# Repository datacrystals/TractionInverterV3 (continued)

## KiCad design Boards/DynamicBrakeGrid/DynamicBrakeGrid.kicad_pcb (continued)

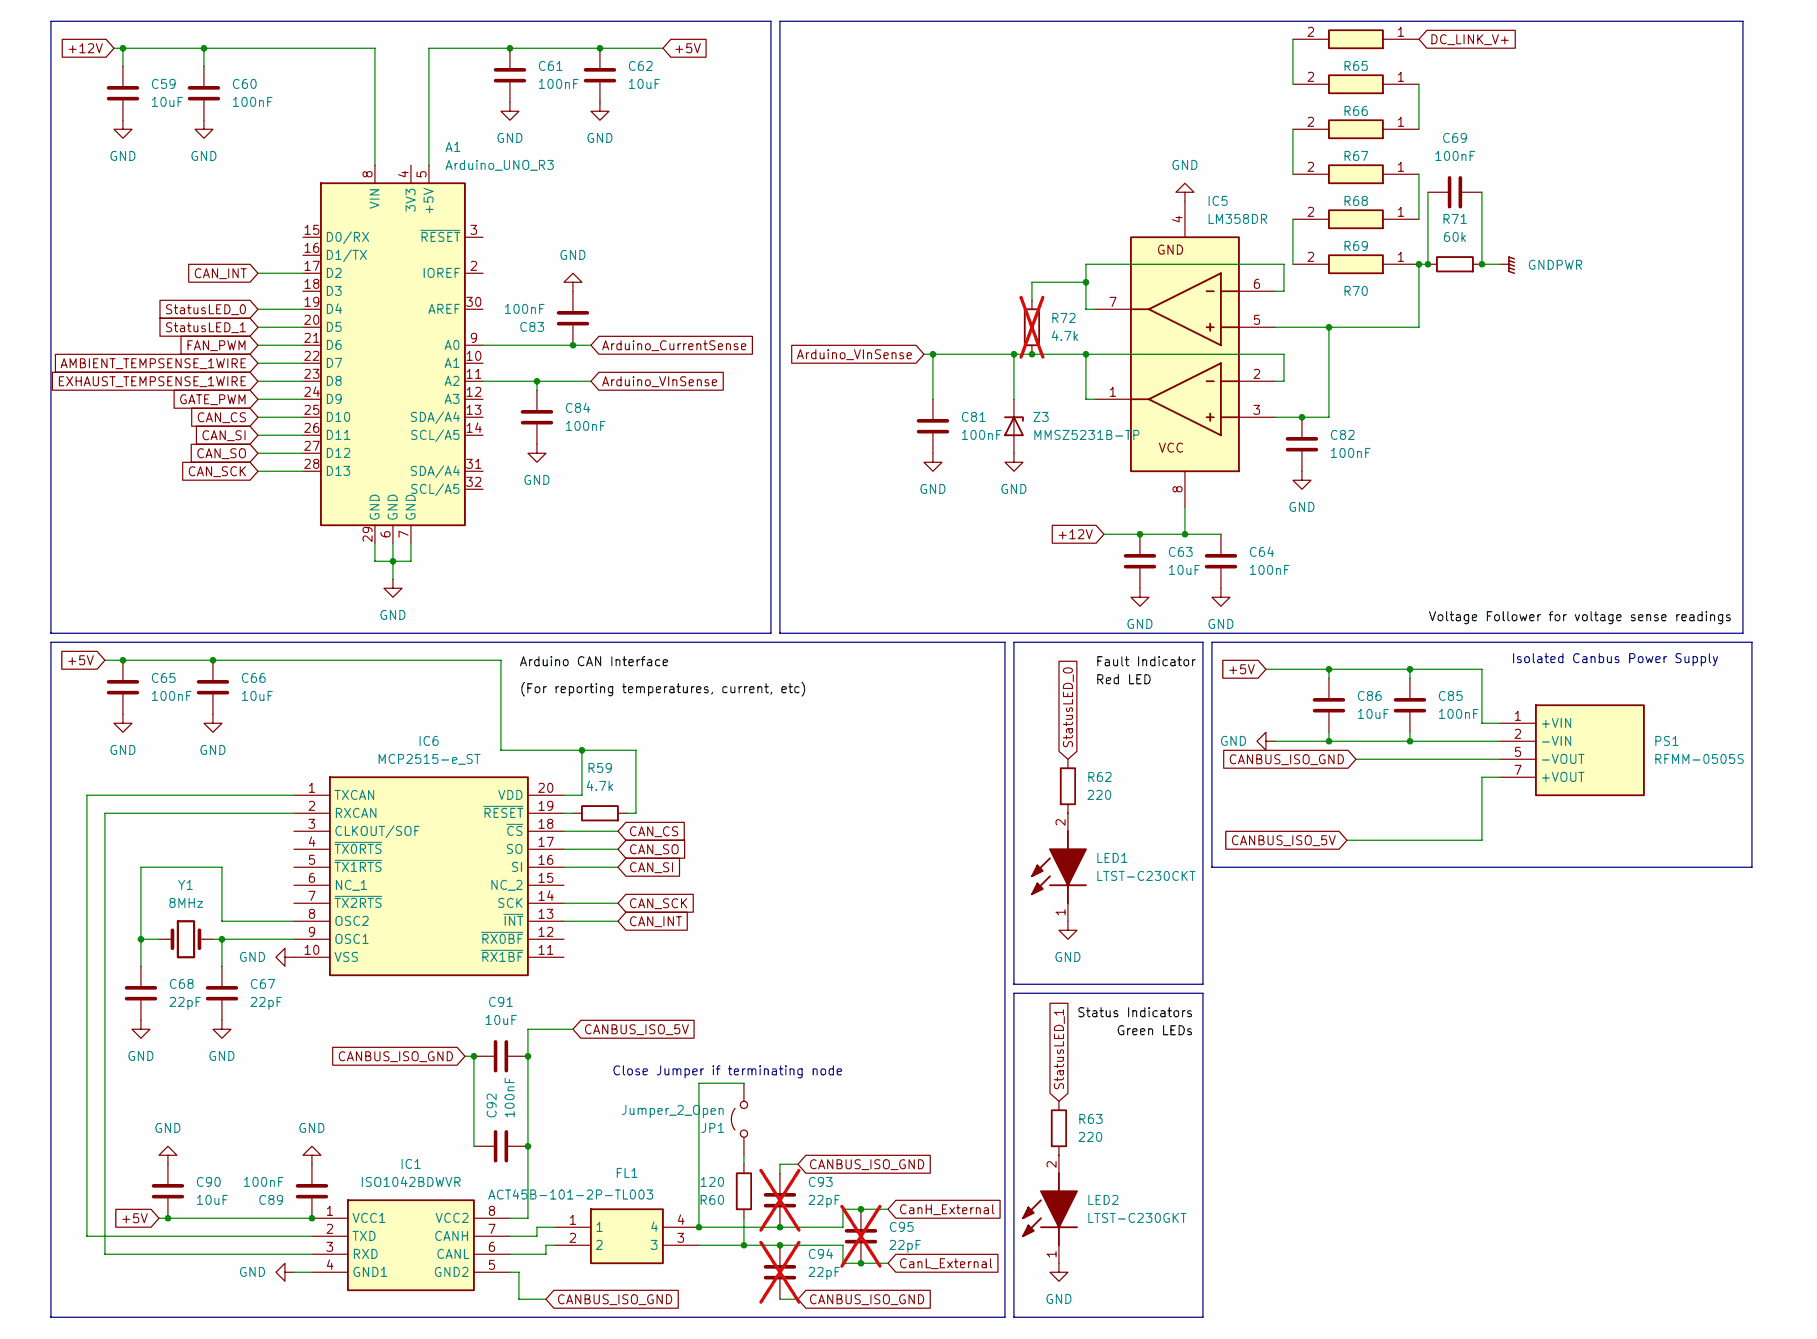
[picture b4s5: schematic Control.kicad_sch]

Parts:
A1: Arduino_UNO_R3; Arduino_UNO_R3_ModifiedCourtyard
C59, C62, C63, C66, C86, C90, C91: 10uF; C_1210_3225Metric_Pad1.33x2.70mm_HandSolder
C60, C61, C64, C65, C69, C81, C82, C83, C84, C85, C89, C92: 100nF; C_1210_3225Metric_Pad1.33x2.70mm_HandSolder
C67, C68: 22pF; C_1210_3225Metric_Pad1.33x2.70mm_HandSolder
C93, C94, C95: 22pF; C_1210_3225Metric_Pad1.33x2.70mm_HandSolder; not fitted
FL1: ACT45B-101-2P-TL003; ACT45B1012PTL003; Mouser Part Number 810-ACT45B1012PTL003
IC1: ISO1042BDWVR; SOIC127P1150X280-8N; Mouser Part Number 595-ISO1042BDWVR
IC5: LM358DR; SOIC127P600X175-8N; Mouser Part Number 595-LM358DR
IC6: MCP2515-e_ST; SOP65P640X120-20N; Mouser Part Number 579-MCP2515-E/ST
JP1: Jumper_2_Open; PinHeader_1x02_P2.54mm_Vertical
LED1: LTST-C230CKT; LEDC3216X120N; Mouser Part Number 859-LTST-C230CKT
LED2: LTST-C230GKT; LEDC3216X120N; Mouser Part Number 859-LTST-C230GKT
PS1: RFMM-0505S; RFMM0505S; Mouser Part Number 919-RFMM-0505S
R59: 4.7k; R_1210_3225Metric_Pad1.30x2.65mm_HandSolder
R60: 120; R_1210_3225Metric_Pad1.30x2.65mm_HandSolder
R62, R63: 220; R_1210_3225Metric_Pad1.30x2.65mm_HandSolder
R65, R66, R67, R68, R69, R70: RC2512JK-071ML; RESC6431X65N; Mouser Part Number 603-RC2512JK-071ML
R71: 60k; R_1210_3225Metric_Pad1.30x2.65mm_HandSolder
R72: 4.7k; R_1210_3225Metric_Pad1.30x2.65mm_HandSolder; not fitted
Y1: 8MHz; Crystal_HC49-4H_Vertical
Z3: MMSZ5231B-TP; SOD3716X135N; Mouser Part Number 833-MMSZ5231B-TP

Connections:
+5V: A1.5 (+5V), C61.1, C62.1, C65.1, C66.1, C85.1, C86.1, C89.1, C90.2, IC1.1 (VCC1), IC6.20 (VDD), PS1.1 (+VIN), R59.2; also elsewhere on the board
+12V: A1.8 (VIN), C59.1, C60.1, C63.1, C64.1, IC5.8 (V+); also elsewhere on the board
AMBIENT_TEMPSENSE_1WIRE: A1.22 (D7); also elsewhere on the board
Arduino_CurrentSense: A1.9 (A0), C83.1; also elsewhere on the board
Arduino_VInSense: A1.11 (A2), C81.1, C84.1, IC5.1 (OUT1), IC5.2 (IN1-), R72.1, Z3.1 (K)
CANBUS_ISO_5V: C91.1, C92.2, IC1.8 (VCC2), PS1.7 (+VOUT)
CANBUS_ISO_GND: C91.2, C92.1, C93.1, C94.2, IC1.5 (GND2), PS1.5 (-VOUT); also elsewhere on the board
CAN_CS: A1.25 (D10), IC6.18 (~CS)
CAN_INT: A1.17 (D2), IC6.13 (~INT)
CAN_SCK: A1.28 (D13), IC6.14 (SCK)
CAN_SI: A1.26 (D11), IC6.16 (SI)
CAN_SO: A1.27 (D12), IC6.17 (SO)
CanH_External: C93.2, C95.1, FL1.4, JP1.2 (B); also elsewhere on the board
CanL_External: C94.1, C95.2, FL1.3, R60.2; also elsewhere on the board
DC_LINK_V+: R65.1; also elsewhere on the board
EXHAUST_TEMPSENSE_1WIRE: A1.23 (D8); also elsewhere on the board
FAN_PWM: A1.21 (D6); also elsewhere on the board
GATE_PWM: A1.24 (D9); also elsewhere on the board
GND: A1.6 (GND), A1.7 (GND), A1.29 (GND), C59.2, C60.2, C61.2, C62.2, C63.2, C64.2, C65.2, C66.2, C67.2, C68.2, C81.2, C82.2, C83.2, C84.2, C85.2, C86.2, C89.2, C90.1, IC1.4 (GND1), IC5.4 (V-), IC6.10 (VSS), LED1.1 (K), LED2.1 (K), PS1.2 (-VIN), Z3.2 (A); also elsewhere on the board
GNDPWR: C69.2, R71.2; also elsewhere on the board
unnamed: FL1.1, IC1.7 (CANH)
unnamed: FL1.2, IC1.6 (CANL)
unnamed: IC1.3 (RXD), IC6.2 (RXCAN)
unnamed: IC1.2 (TXD), IC6.1 (TXCAN)
unnamed: C69.1, C82.1, IC5.3 (IN1+), IC5.5 (IN2+), R70.1, R71.1
unnamed: IC5.6 (IN2-), IC5.7 (OUT2), R72.2
unnamed: C67.1, IC6.9 (OSC1), Y1.2
unnamed: C68.1, IC6.8 (OSC2), Y1.1
unnamed: IC6.19 (~RESET), R59.1
unnamed: JP1.1 (A), R60.1
unnamed: LED1.2 (A), R62.2
unnamed: LED2.2 (A), R63.2
unnamed: R65.2, R66.2
unnamed: R66.1, R67.1
unnamed: R67.2, R68.2
unnamed: R68.1, R69.1
unnamed: R69.2, R70.2
StatusLED_0: A1.19 (D4), R62.1
StatusLED_1: A1.20 (D5), R63.1

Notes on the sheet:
Close Jumper if terminating node
Isolated Canbus Power Supply

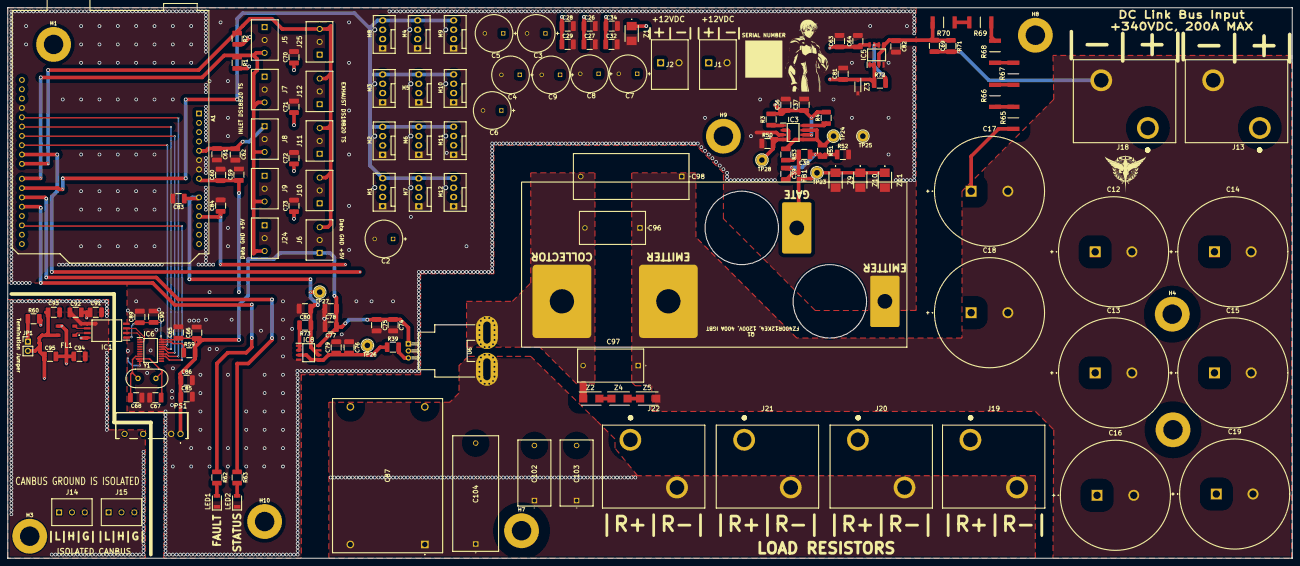
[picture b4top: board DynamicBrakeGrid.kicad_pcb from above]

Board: 4 copper layers, 350.0 x 150.0 mm, 159 parts (0 on the bottom side), 52 nets.

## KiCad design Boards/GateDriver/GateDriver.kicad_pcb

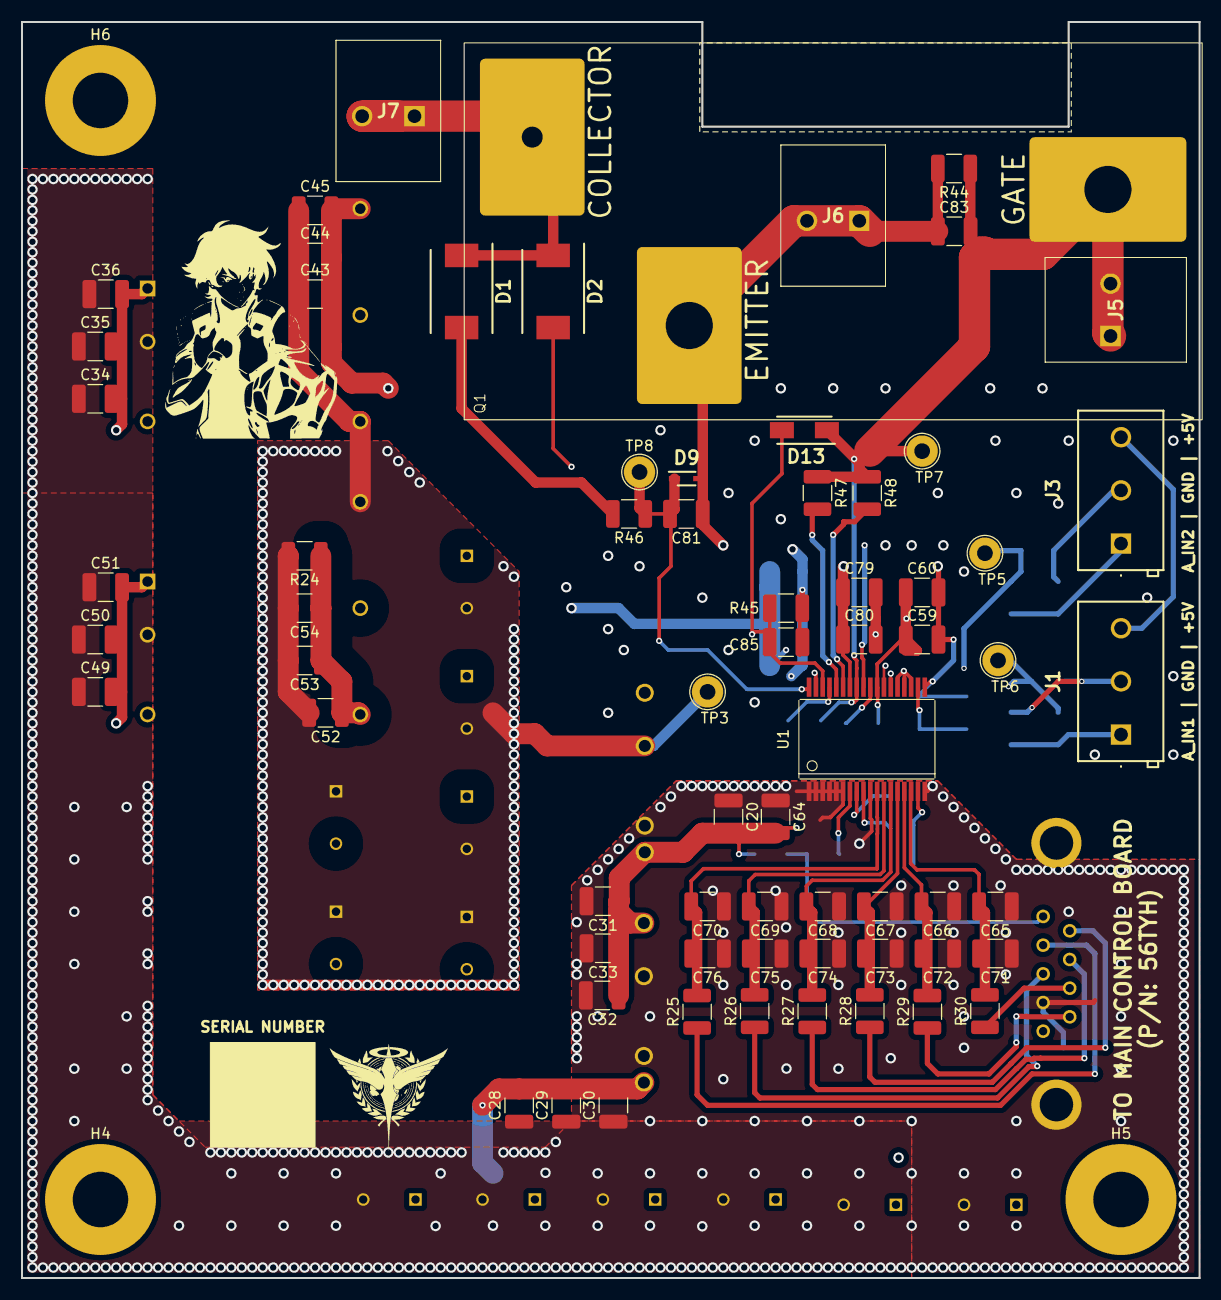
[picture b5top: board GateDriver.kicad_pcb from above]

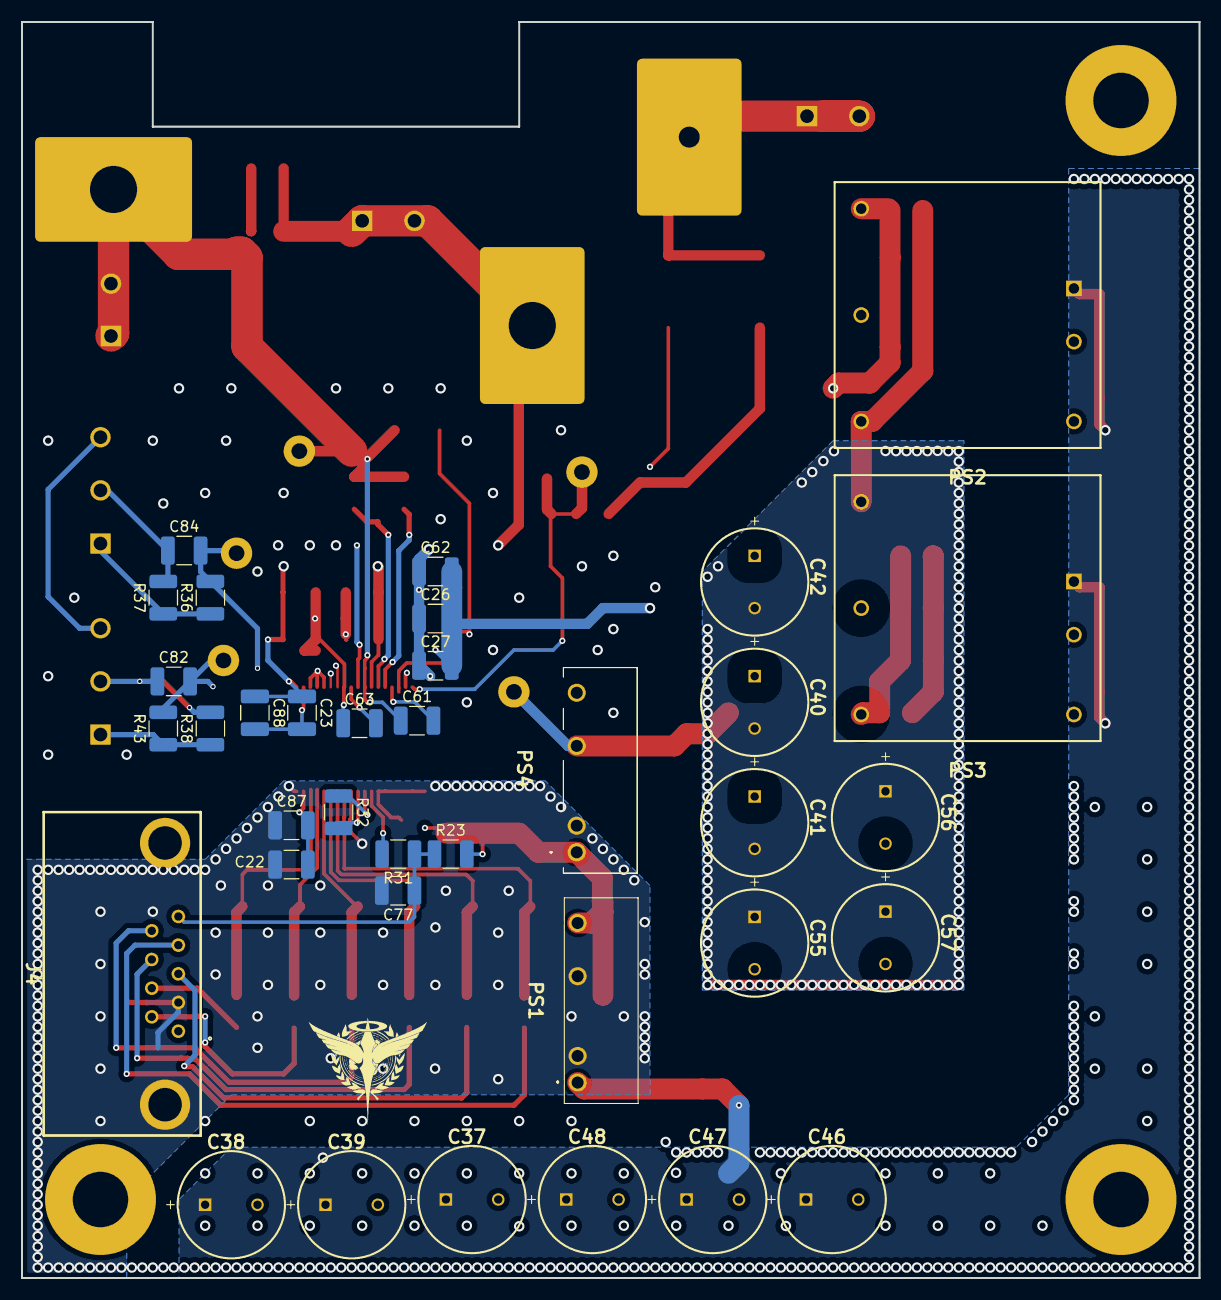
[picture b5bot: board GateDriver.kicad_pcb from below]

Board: 4 copper layers, 112.5 x 120.0 mm, 106 parts (36 on the bottom side), 37 nets.

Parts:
C20, C26, C29, C32, C35, C44, C50, C53, C59, C63, C80: 1uF; C_1210_3225Metric_Pad1.33x2.70mm_HandSolder
C22, C23: 4.7uF; C_1210_3225Metric_Pad1.33x2.70mm_HandSolder
C27, C30, C33, C36, C45, C51, C52, C60, C61, C64, C79, C83, C87, C88: 100nF; C_1210_3225Metric_Pad1.33x2.70mm_HandSolder
C28, C31, C34, C43, C49, C54, C62: 10uF; C_1210_3225Metric_Pad1.33x2.70mm_HandSolder
C37, C38, C39, C40, C41, C42, C46, C47, C48, C55, C56, C57: UVY1E102MPD1TD; CAPPRD500W60D1025H1750
C65, C66, C67, C68, C69, C70: 10pF; C_1210_3225Metric_Pad1.33x2.70mm_HandSolder
C71, C72, C73, C74, C75, C76, C77, C81: 100pF; C_1210_3225Metric_Pad1.33x2.70mm_HandSolder
C82, C84: 10nF; C_1210_3225Metric_Pad1.33x2.70mm_HandSolder
C85: 2.2nF; C_1210_3225Metric_Pad1.33x2.70mm_HandSolder
D1, D2: S3N; DIOM8059X265N
D9: BAT54WS-7-F; SOD2513X120N
D13: MBRA340T3G; DIOM5226X220N
H4, H5, H6: MountingHole_Pad_MP; MountingHole_5.3mm_M5_Pad
J1, J3: 1548129
J4: 5-106505-2; 5-106505-2_3
J5, J6, J7: 1987724
PS1: RKE-1205S_H; RKE1205SH
PS2: REC10K-2415SAW_H2; REC10K-AW
PS3: REC10K-2409SAW_H2; REC10K-AW
PS4: RFMM-0505S; RFMM0505S
Q1: CM600HA-24H-Gate
R23, R32, R37, R38: 10k; R_1210_3225Metric_Pad1.30x2.65mm_HandSolder
R24, R36, R43: 0; R_1210_3225Metric_Pad1.30x2.65mm_HandSolder
R25, R26, R27, R28, R29, R30, R31, R45: 100; R_1210_3225Metric_Pad1.30x2.65mm_HandSolder
R44, R46: 1k; R_1210_3225Metric_Pad1.30x2.65mm_HandSolder
R47, R48: 1.5; R_1210_3225Metric_Pad1.30x2.65mm_HandSolder
TP3, TP5, TP6, TP7, TP8: TestPoint; TestPoint_Loop_D2.54mm_Drill1.5mm_Beaded
U1: UCC5870QDWJRQ1; DWJ0036A

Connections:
+5V: C20.2, C31.1, C32.1, C33.1, C64.2, PS1.7 (+VOUT), PS4.1 (+VIN), R23.2, R32.2, U1.9 (VCC1)
+5VP: J1.3, J3.3, PS4.7 (+VOUT)
+12V: C28.2, C29.2, C30.2, C34.2, C35.2, C36.2, C37.1 (+), C38.1 (+), C39.1 (+), C46.1 (+), C47.1 (+), C48.1 (+), C49.2, C50.2, C51.2, J4.1, PS1.1 (+VIN), PS2.1 (+VIN), PS3.1 (+VIN)
ANALOG_INPUT_1: J1.1, R38.1, R43.1
ANALOG_INPUT_2: J3.1, R36.1, R37.1
ANALOG_SENSE_1: C82.2, R43.2, TP6.1, U1.25 (AI2)
ANALOG_SENSE_2: C84.2, R36.2, TP5.1, U1.24 (AI3)
FAULT: C77.1, J4.5, R23.1, R31.1
FILTERED_GATE_DRIVE+: C69.2, C75.2, R26.2, U1.12 (IN+)
FILTERED_GATE_DRIVE-: C70.2, C76.2, R25.2, U1.11 (IN-)
FILTERED_SDI: C66.2, C72.2, R29.2, U1.15 (SDI)
FILTERED_SDO: C65.2, C71.2, R30.2, U1.16 (SDO)
FILTERED_SPI_CLK: C68.2, C74.2, R27.2, U1.13 (CLK)
FILTERED_SPI_CS: C67.2, C73.2, R28.2, U1.14 (nCS)
GATE_DRIVE+: J4.3, R26.1
GATE_DRIVE-: J4.4, R25.1
GND: C20.1, C22.1, C28.1, C29.1, C30.1, C31.2, C32.2, C33.2, C34.1, C35.1, C36.1, C37.2 (-), C38.2 (-), C39.2 (-), C46.2 (-), C47.2 (-), C48.2 (-), C49.1, C50.1, C51.1, C64.1, C65.1, C66.1, C67.1, C68.1, C69.1, C70.1, C71.1, C72.1, C73.1, C74.1, C75.1, C76.1, C77.2, C87.1, J4.2, J4.10, J4.11, PS1.2 (-VIN), PS1.5 (-VOUT), PS2.2 (-VIN), PS3.2 (-VIN), PS4.2 (-VIN), U1.1 (GND1), U1.2 (NC), U1.3 (NC), U1.4 (NC), U1.5 (NC), U1.6 (ASC_EN), U1.10 (ASC), U1.18 (GND1)
IGBT_COLLECTOR: D1.1 (K), D2.1 (K), J7.1, J7.2, Q1.1 (C)
IGBT_EMITTER: C26.1, C27.1, C40.2 (-), C41.2 (-), C42.2 (-), C43.1, C44.1, C45.1, C52.2, C53.2, C54.2, C55.1 (+), C56.1 (+), C57.1 (+), C59.1, C60.1, C62.1, C63.1, C81.1, C82.1, C83.1, C84.1, C85.2, D9.2 (A), J1.2, J3.2, J6.1, J6.2, PS2.4 (-VOUT), PS3.6 (+VOUT), PS4.5 (-VOUT), Q1.2 (E), R24.2, R37.2, R38.2, R44.2, R45.1, TP3.1, U1.21 (AI6), U1.22 (AI5), U1.23 (AI4), U1.26 (AI1), U1.28 (GND2)
IGBT_GATE: C61.1, C83.2, D13.1 (K), J5.1, J5.2, Q1.3 (G), R44.1, R47.1, R48.1, TP7.1, U1.29 (CLAMP)
ISO_GATE_DRIVE_+15V: C26.2, C27.2, C40.1 (+), C41.1 (+), C42.1 (+), C43.2, C44.2, C45.2, C62.2, C79.2, C80.2, PS2.6 (+VOUT), U1.35 (VCC2)
ISO_GATE_DRIVE_-9V: C23.1, C52.1, C53.1, C54.1, C55.2 (-), C56.2 (-), C57.2 (-), C59.2, C60.2, C79.1, C80.1, C88.1, PS3.4 (-VOUT), R24.1, U1.19 (VEE2), U1.30 (VEE2)
unnamed: D1.2 (A), R46.2
unnamed: C81.2, D9.1 (K), R46.1, TP8.1, U1.36 (DESAT)
unnamed: C85.1, D2.2 (A), D13.2 (A), R45.2, U1.34 (VCECLP)
unnamed: R47.2, U1.32 (OUTH)
unnamed: R48.2, U1.31 (OUTL)
unnamed: C61.2, U1.33 (VBST)
unnamed: C63.2, U1.27 (VREF)
unnamed: C22.2, C87.2, U1.17 (VREG1)
unnamed: C23.2, C88.2, U1.20 (VREG2)
unnamed: R31.2, U1.7 (nFLT1)
unnamed: R32.1, U1.8 (nFLT2_DOUT)
SDI: J4.6, R29.1
SDO: J4.7, R30.1
SPI_CLK: J4.8, R27.1
SPI_CS: J4.9, R28.1

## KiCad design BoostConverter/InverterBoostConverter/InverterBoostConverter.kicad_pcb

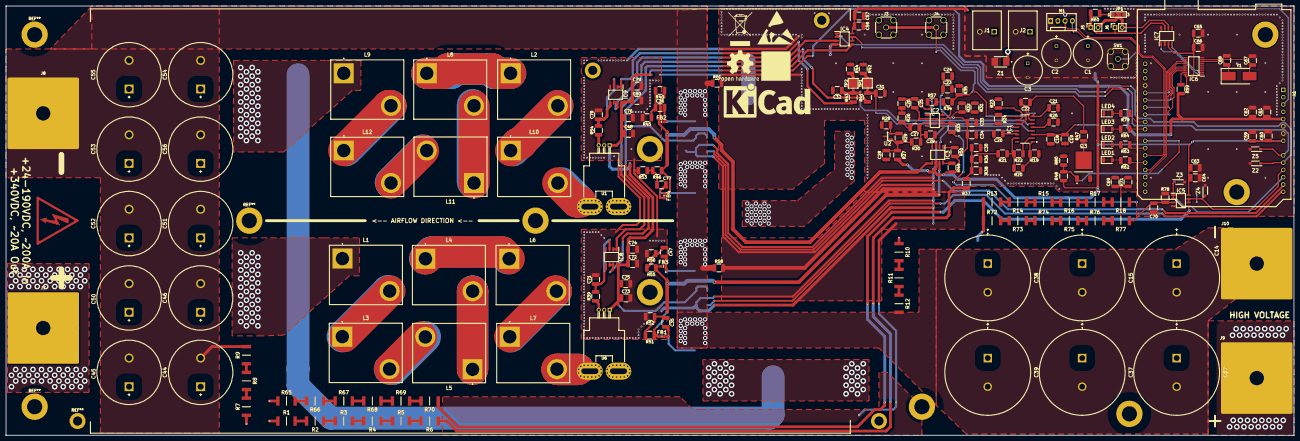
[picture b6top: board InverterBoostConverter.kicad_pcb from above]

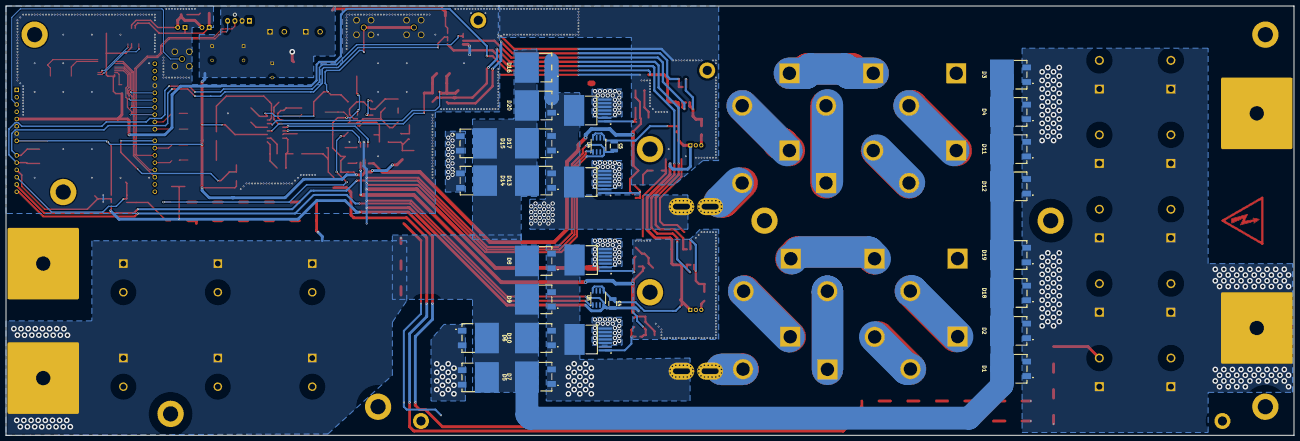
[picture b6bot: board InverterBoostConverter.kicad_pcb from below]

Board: 2 copper layers, 450.0 x 150.0 mm, 227 parts (28 on the bottom side), 121 nets.

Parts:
A1: Arduino_UNO_R3; Arduino_UNO_R3_ModifiedCourtyard
C1, C2, C3: 1000uF; CAPPRD500W60D1025H1750
C4, C5, C20, C22: 1uF; C_1210_3225Metric_Pad1.33x2.70mm_HandSolder
C14, C15, C17, C37, C38, C39: 75uF; ALH82A750CB600
C18, C23, C34, C48, C58, C60, C61, C64, C65, C69, C70, C73, C74, C79: 100nF; C_1210_3225Metric_Pad1.33x2.70mm_HandSolder
C19, C24, C33, C57, C59, C62, C63, C66, C72, C75, C76, C80: 10uF; C_1210_3225Metric_Pad1.33x2.70mm_HandSolder
C21: 180pF; C_1210_3225Metric_Pad1.33x2.70mm_HandSolder
C25: 10nF; C_1210_3225Metric_Pad1.33x2.70mm_HandSolder
C26: C_1210_3225Metric_Pad1.33x2.70mm_HandSolder
C27, C29, C30, C35, C36, C47, C77: 1nF; C_1210_3225Metric_Pad1.33x2.70mm_HandSolder
C28: 4.7uF; C_1210_3225Metric_Pad1.33x2.70mm_HandSolder
C31, C32, C71, C78: 470pF; C_1210_3225Metric_Pad1.33x2.70mm_HandSolder
C44, C45, C46, C50, C51, C52, C53, C54, C55, C56: 330uF; CAPPRD1000W190D2250H2700
C67, C68: 22pF; C_1210_3225Metric_Pad1.33x2.70mm_HandSolder
D1, D2, D3, D4, D5, D6, D7, D8, D9, D10, D11, D12, D13, D14, D15, D16, D17, D18, D19, D20: VS-30CDU06HM3_I; VS30CDU06HM3I
FB1, FB2, FB3, FB4: FBMJ1608HS220NTR; BEADC1608X100N
IC1: UCC28220D
IC2, IC4, IC5, IC8, IC9: LM358DR; SOIC127P600X175-8N
IC3: UCC27424QDRQ1; SOIC127P600X175-8N
IC6: MCP2515-e_ST; SOP65P640X120-20N
IC7: TJA1050T_CM,118; SOIC127P600X175-8N
J1, J2: 1987724
J3, J4: Conn_Coaxial; SMA_Wurth_60312002114503_Vertical
J5, J6: Conn_01x02_Pin; PinSocket_1x02_P2.54mm_Vertical
J7, J8, J9, J10: WireSolderJoint
JP1: Jumper_2_Bridged; SolderJumper-3_P2.0mm_Open_TrianglePad1.0x1.5mm_NumberLabels
L1, L2, L3, L4, L5, L6, L7, L8, L9, L10, L11, L12: IHDM1008BCEV2R2M20
LED1: LTST-C230CKT; LEDC3216X120N
LED2, LED3, LED4: LTST-C230GKT; LEDC3216X120N
M1: Fan_4pin; FanPinHeader_1x04_P2.54mm_Vertical
Q1, Q2, Q4, Q5: IMBG65R015M2H; TO127P1500X470-8N-2-V1
Q3: SIHFR120-GE3; SIHFR120GE3
R1, R2, R3, R4, R5, R6, R7, R8, R9, R10, R11, R12, R13, R14, R15, R16, R17, R18, R65, R66, R67, R68, R69, R72, R73, R74, R75, R76: RC2512JK-071ML; RESC6431X65N
R19: 12.79k; R_1210_3225Metric_Pad1.30x2.65mm_HandSolder
R20: 101.85k; R_1210_3225Metric_Pad1.30x2.65mm_HandSolder
R21: 149.21k; R_1210_3225Metric_Pad1.30x2.65mm_HandSolder
R22, R26, R37, R49, R50, R80: 100k; R_1210_3225Metric_Pad1.30x2.65mm_HandSolder
R23: 40.8k; R_1210_3225Metric_Pad1.30x2.65mm_HandSolder
R24: 10.2k; R_1210_3225Metric_Pad1.30x2.65mm_HandSolder
R25: 7k; R_1210_3225Metric_Pad1.30x2.65mm_HandSolder
R27: 5.6k; R_1210_3225Metric_Pad1.30x2.65mm_HandSolder
R28, R40, R46, R47, R51, R55, R59: 10k; R_1210_3225Metric_Pad1.30x2.65mm_HandSolder
R29, R30, R41, R43, R58, R61: 0; R_1210_3225Metric_Pad1.30x2.65mm_HandSolder
R31: 45.00k; R_1210_3225Metric_Pad1.30x2.65mm_HandSolder
R32, R71: 120k; R_1210_3225Metric_Pad1.30x2.65mm_HandSolder
R33: 28k; R_1210_3225Metric_Pad1.30x2.65mm_HandSolder
R34, R35, R57: 1k; R_1210_3225Metric_Pad1.30x2.65mm_HandSolder
R36: 800.00k; R_1210_3225Metric_Pad1.30x2.65mm_HandSolder
R38, R42, R44: R_1210_3225Metric_Pad1.30x2.65mm_HandSolder
R39, R54: 4.7k; R_1210_3225Metric_Pad1.30x2.65mm_HandSolder
R45, R52, R53, R56: 1; R_1210_3225Metric_Pad1.30x2.65mm_HandSolder
R48: 300k; R_1210_3225Metric_Pad1.30x2.65mm_HandSolder
R60: 120; R_1210_3225Metric_Pad1.30x2.65mm_HandSolder
R62, R63, R64, R79: 220; R_1210_3225Metric_Pad1.30x2.65mm_HandSolder
R70, R77: 1M; RESC6431X65N
R78: 40k; R_1210_3225Metric_Pad1.30x2.65mm_HandSolder
SW1: SW_Push; SMA_Wurth_60312002114503_Vertical
TP1, TP2: TestPoint; TestPoint_Pad_3.0x3.0mm
U1, U6: ACS758xCB-200U-PFF; Allegro_CB_PFF
U2: TL431AIDBZR; SOT95P237X112-3N
U4, U5: TMP36xS; SOIC-8_3.9x4.9mm_P1.27mm
Y1: 8MHz; Crystal_SMD_7050-2Pin_7.0x5.0mm_HandSoldering
Z1: 1SMB2EZ15_R1_00001
Z2, Z3, Z4, Z5: MMSZ5231B-TP; SOD3716X135N

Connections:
+5V: A1.5 (+5V), C4.1, C5.1, C48.1, C61.1, C62.1, C65.1, C66.1, C72.1, C73.1, C74.1, C75.1, C76.1, C79.1, C80.1, IC6.20 (VDD), IC7.3 (VCC), IC8.8 (V+), IC9.8 (V+), R59.2, U1.1 (VCC), U4.5 (~SHUTDOWN), U4.8 (+Vs), U5.5 (~SHUTDOWN), U5.8 (+Vs), U6.1 (VCC)
+12V: A1.8 (VIN), C1.1 (+), C2.1 (+), C3.1 (+), C18.1, C19.1, C23.1, C24.1, C33.1, C34.1, C57.1, C58.1, C59.1, C60.1, C63.1, C64.1, IC1.3 (VDD), IC2.8 (V+), IC3.6 (VDD), IC4.8 (V+), IC5.8 (V+), J1.1, J2.1, M1.2 (+), R27.2, R48.2, R49.2, R50.2, Z1.1 (K)
+VBus_In: C44.1 (+), C45.1 (+), C46.1 (+), C50.1 (+), C51.1 (+), C52.1 (+), C53.1 (+), C54.1 (+), C55.1 (+), C56.1 (+), D1.1 (A), D1.2 (A), D2.1 (A), D2.2 (A), D3.1 (A), D3.2 (A), D4.1 (A), D4.2 (A), D11.1 (A), D11.2 (A), D12.1 (A), D12.2 (A), D18.1 (A), D18.2 (A), D19.1 (A), D19.2 (A), J7.1, L1.1, L9.1, R1.1, R7.1, R65.1
+VBus_In_Sense: R6.1, R37.2
+VBus_Out: C14.1, C15.1, C17.1, C37.1, C38.1, C39.1, D1.3 (K), D2.3 (K), D3.3 (K), D4.3 (K), D5.3 (K), D6.3 (K), D7.3 (K), D8.3 (K), D9.3 (K), D10.3 (K), D11.3 (K), D12.3 (K), D13.3 (K), D14.3 (K), D15.3 (K), D16.3 (K), D17.3 (K), D18.3 (K), D19.3 (K), D20.3 (K), J9.1, R10.1, R13.1, R72.1
+VBus_Out_Sense: R18.1, R33.2
-VBus_In: C14.2, C15.2, C17.2, C37.2, C38.2, C39.2, C44.2 (-), C45.2 (-), C46.2 (-), C50.2 (-), C51.2 (-), C52.2 (-), C53.2 (-), C54.2 (-), C55.2 (-), C56.2 (-), J8.1, J10.1, Q1.3 (POWER_SOURCE_1), Q1.4 (POWER_SOURCE_2), Q1.5 (POWER_SOURCE_3), Q1.6 (POWER_SOURCE_4), Q1.7 (POWER_SOURCE_5), Q2.3 (POWER_SOURCE_1), Q2.4 (POWER_SOURCE_2), Q2.5 (POWER_SOURCE_3), Q2.6 (POWER_SOURCE_4), Q2.7 (POWER_SOURCE_5), Q4.3 (POWER_SOURCE_1), Q4.4 (POWER_SOURCE_2), Q4.5 (POWER_SOURCE_3), Q4.6 (POWER_SOURCE_4), Q4.7 (POWER_SOURCE_5), Q5.3 (POWER_SOURCE_1), Q5.4 (POWER_SOURCE_2), Q5.5 (POWER_SOURCE_3), Q5.6 (POWER_SOURCE_4), Q5.7 (POWER_SOURCE_5), R9.2, R12.2, R58.1, R61.1
Arduino_Ph1CM: A1.9 (A0), IC4.6 (IN2-), IC4.7 (OUT2), Z5.1 (K)
Arduino_Ph1Curr: IC4.5 (IN2+), IC8.6 (IN2-), IC8.7 (OUT2)
Arduino_Ph2CM: A1.10 (A1), IC4.1 (OUT1), IC4.2 (IN1-), Z2.1 (K)
Arduino_Ph2Curr: IC4.3 (IN1+), IC9.6 (IN2-), IC9.7 (OUT2)
Arduino_Temp1: A1.13 (SDA/A4), U4.1 (V_{OUT})
Arduino_Temp2: A1.14 (SCL/A5), U5.1 (V_{OUT})
Arduino_VOutSense: A1.12 (A3), IC5.1 (OUT1), IC5.2 (IN1-), Z3.1 (K)
Arduino_VinSense: A1.11 (A2), IC5.6 (IN2-), IC5.7 (OUT2), Z4.1 (K)
CAN_CS: A1.25 (D10), IC6.18 (~CS)
CAN_INT: A1.17 (D2), IC6.13 (~INT)
CAN_SCK: A1.28 (D13), IC6.14 (SCK)
CAN_SI: A1.26 (D11), IC6.16 (SI)
CAN_SO: A1.27 (D12), IC6.17 (SO)
CanH_External: IC7.7 (CANH), J5.1, J6.1, R60.2
CanL_External: IC7.6 (CANL), J5.2, J6.2, JP1.2 (B)
FanPWM: A1.20 (D5), M1.4 (PWM)
FanTach: A1.18 (D3), M1.3 (Tacho)
unnamed: A1.3 (~RESET), SW1.1
unnamed: C26.2, R26.1
unnamed: C30.1, R21.2, R36.2, R37.1, R38.2
unnamed: C35.1, R51.2, R52.1
unnamed: C36.1, R40.2, R45.1
unnamed: C47.1, R55.2, R56.1
unnamed: C77.1, R46.2, R53.1
unnamed: IC1.10 (CHG), R23.1
unnamed: C31.1, IC1.4 (CS1), R41.2, R42.2, TP1.1
unnamed: C32.1, IC1.6 (CS2), R43.2, R44.2, TP2.1
unnamed: IC1.9 (DISCHG), R24.1
unnamed: IC1.2 (LINEHYS), R22.1
unnamed: IC1.1 (LINEOV), R19.2, R20.1
unnamed: IC1.15 (LINEUV), R20.2, R21.1, R22.2
unnamed: C20.1, IC1.14 (REF)
unnamed: IC1.5 (SLOPE), R25.1
unnamed: C22.1, IC1.7 (SS), R47.2
unnamed: C27.1, C29.2, IC2.3 (IN1+), IC2.5 (IN2+), R30.1
unnamed: C25.2, C27.2, IC2.2 (IN1-), IC2.6 (IN2-), R26.2, R31.2, R32.2, R33.1
unnamed: IC2.1 (OUT1), R57.1
unnamed: C25.1, C26.1, IC2.7 (OUT2), R34.2, R57.2
unnamed: IC3.1 (ENBA), R50.1
unnamed: IC3.8 (ENBB), R49.1
unnamed: C70.1, IC5.3 (IN1+), R77.1, R78.1
unnamed: C69.1, IC5.5 (IN2+), R70.1, R71.1
unnamed: C67.1, IC6.9 (OSC1), Y1.2
unnamed: C68.1, IC6.8 (OSC2), Y1.1
unnamed: IC6.2 (RXCAN), IC7.4 (RXD)
unnamed: IC6.1 (TXCAN), IC7.1 (TXD)
unnamed: IC6.19 (~RESET), R59.1
unnamed: C71.1, IC8.3 (IN1+), IC8.5 (IN2+), R39.2
unnamed: C78.1, IC9.3 (IN1+), IC9.5 (IN2+), R54.2
unnamed: JP1.1 (A), R60.1
unnamed: L1.2, L3.1
unnamed: L2.1, L8.1
unnamed: L3.2, L5.2
unnamed: L4.1, L6.1
unnamed: L4.2, L5.1
unnamed: L6.2, L7.1
unnamed: L2.2, L10.1
unnamed: L8.2, L11.1
unnamed: L11.2, L12.2
unnamed: L9.2, L12.1
unnamed: LED1.2 (A), R62.2
unnamed: LED2.2 (A), R63.2
unnamed: LED3.2 (A), R64.2
unnamed: LED4.2 (A), R79.2
unnamed: D5.1 (A), D5.2 (A), D6.1 (A), D6.2 (A), D7.1 (A), D7.2 (A), D8.1 (A), D8.2 (A), D9.1 (A), D9.2 (A), D10.1 (A), D10.2 (A), Q1.8 (DRAIN), Q4.8 (DRAIN), U6.5 (IP-)
unnamed: C35.2, FB1.2, Q1.1 (GATE)
unnamed: D13.1 (A), D13.2 (A), D14.1 (A), D14.2 (A), D15.1 (A), D15.2 (A), D16.1 (A), D16.2 (A), D17.1 (A), D17.2 (A), D20.1 (A), D20.2 (A), Q2.8 (DRAIN), Q5.8 (DRAIN), U1.5 (IP-)
unnamed: C36.2, FB2.2, Q2.1 (GATE)
unnamed: Q3.3 (D), R47.1
unnamed: C47.2, FB3.2, Q4.1 (GATE)
unnamed: C77.2, FB4.2, Q5.1 (GATE)
unnamed: R1.2, R2.2
unnamed: R2.1, R3.1
unnamed: R3.2, R4.2
unnamed: R4.1, R5.1
unnamed: R5.2, R6.2
unnamed: R7.2, R8.2
unnamed: R8.1, R9.1
unnamed: R10.2, R11.2
unnamed: R11.1, R12.1
unnamed: R13.2, R14.2
unnamed: R14.1, R15.1
unnamed: R15.2, R16.2
unnamed: R16.1, R17.1
unnamed: R17.2, R18.2
unnamed: R65.2, R66.2
unnamed: R66.1, R67.1
unnamed: R67.2, R68.2
unnamed: R68.1, R69.1
unnamed: R69.2, R70.2
unnamed: R72.2, R73.2
unnamed: R73.1, R74.1
unnamed: R74.2, R75.2
unnamed: R75.1, R76.1
unnamed: R76.2, R77.2
unnamed: L10.2, U1.4 (IP+)
unnamed: R54.1, U1.3 (VIOUT)
unnamed: R28.2, R29.1, U2.2 (REF)
unnamed: L7.2, U6.4 (IP+)
unnamed: R39.1, U6.3 (VIOUT)
Ph1_CurrentSense: IC8.1 (OUT1), IC8.2 (IN1-), R41.1
Ph2_CurrentSense: IC9.1 (OUT1), IC9.2 (IN1-), R43.1
Phase1_Gate: FB1.1, FB3.1, IC3.7 (OUTA), R51.1, R55.1
Phase1_GateGnd: A1.6 (GND), A1.7 (GND), A1.29 (GND), C1.2 (-), C2.2 (-), C3.2 (-), C4.2, C5.2, C18.2, C19.2, C20.2, C21.2, C22.2, C23.2, C24.2, C28.1, C29.1, C30.2, C31.2, C32.2, C33.2, C34.2, C48.2, C57.2, C58.2, C59.2, C60.2, C61.2, C62.2, C63.2, C64.2, C65.2, C66.2, C67.2, C68.2, C69.2, C70.2, C71.2, C72.2, C73.2, C74.2, C75.2, C76.2, C78.2, C79.2, C80.2, IC1.11 (GND), IC2.4 (V-), IC3.3 (GND), IC4.4 (V-), IC5.4 (V-), IC6.10 (VSS), IC7.2 (GND), IC7.8 (S), IC8.4 (V-), IC9.4 (V-), J1.2, J2.2, J3.2 (Ext), J4.2 (Ext), LED1.1 (K), LED2.1 (K), LED3.1 (K), LED4.1 (K), M1.1 (-), Q3.2 (S), R19.1, R23.2, R24.2, R25.2, R28.1, R31.1, R32.1, R35.1, R36.1, R38.1, R42.1, R44.1, R45.2, R52.2, R53.2, R56.2, R58.2, R61.2, R71.2, R78.2, R80.1, SW1.2, U1.2 (GND), U2.3 (ANODE), U4.4 (GND), U5.4 (GND), U6.2 (GND), Z1.2 (A), Z2.2 (A), Z3.2 (A), Z4.2 (A), Z5.2 (A)
Phase1_PWM: IC1.13 (OUT1), IC3.2 (INA)
Phase2_Gate: FB2.1, FB4.1, IC3.5 (OUTB), R40.1, R46.1
Phase2_PWM: IC1.12 (OUT2), IC3.4 (INB)
RegulatorEnable_L: A1.22 (D7), Q3.1 (G), R48.1, R80.2
StatusLED_0: A1.19 (D4), R62.1
StatusLED_1: A1.21 (D6), R63.1
StatusLED_2: A1.23 (D8), R64.1
StatusLED_3: A1.24 (D9), R79.1
V_Ref: C28.2, R27.1, R29.2, R30.2, U2.1 (CATHODE)
VoltageFeedback_Multiboard: C21.1, IC1.8 (CTRL), J3.1 (In), J4.1 (In), R34.1, R35.2
